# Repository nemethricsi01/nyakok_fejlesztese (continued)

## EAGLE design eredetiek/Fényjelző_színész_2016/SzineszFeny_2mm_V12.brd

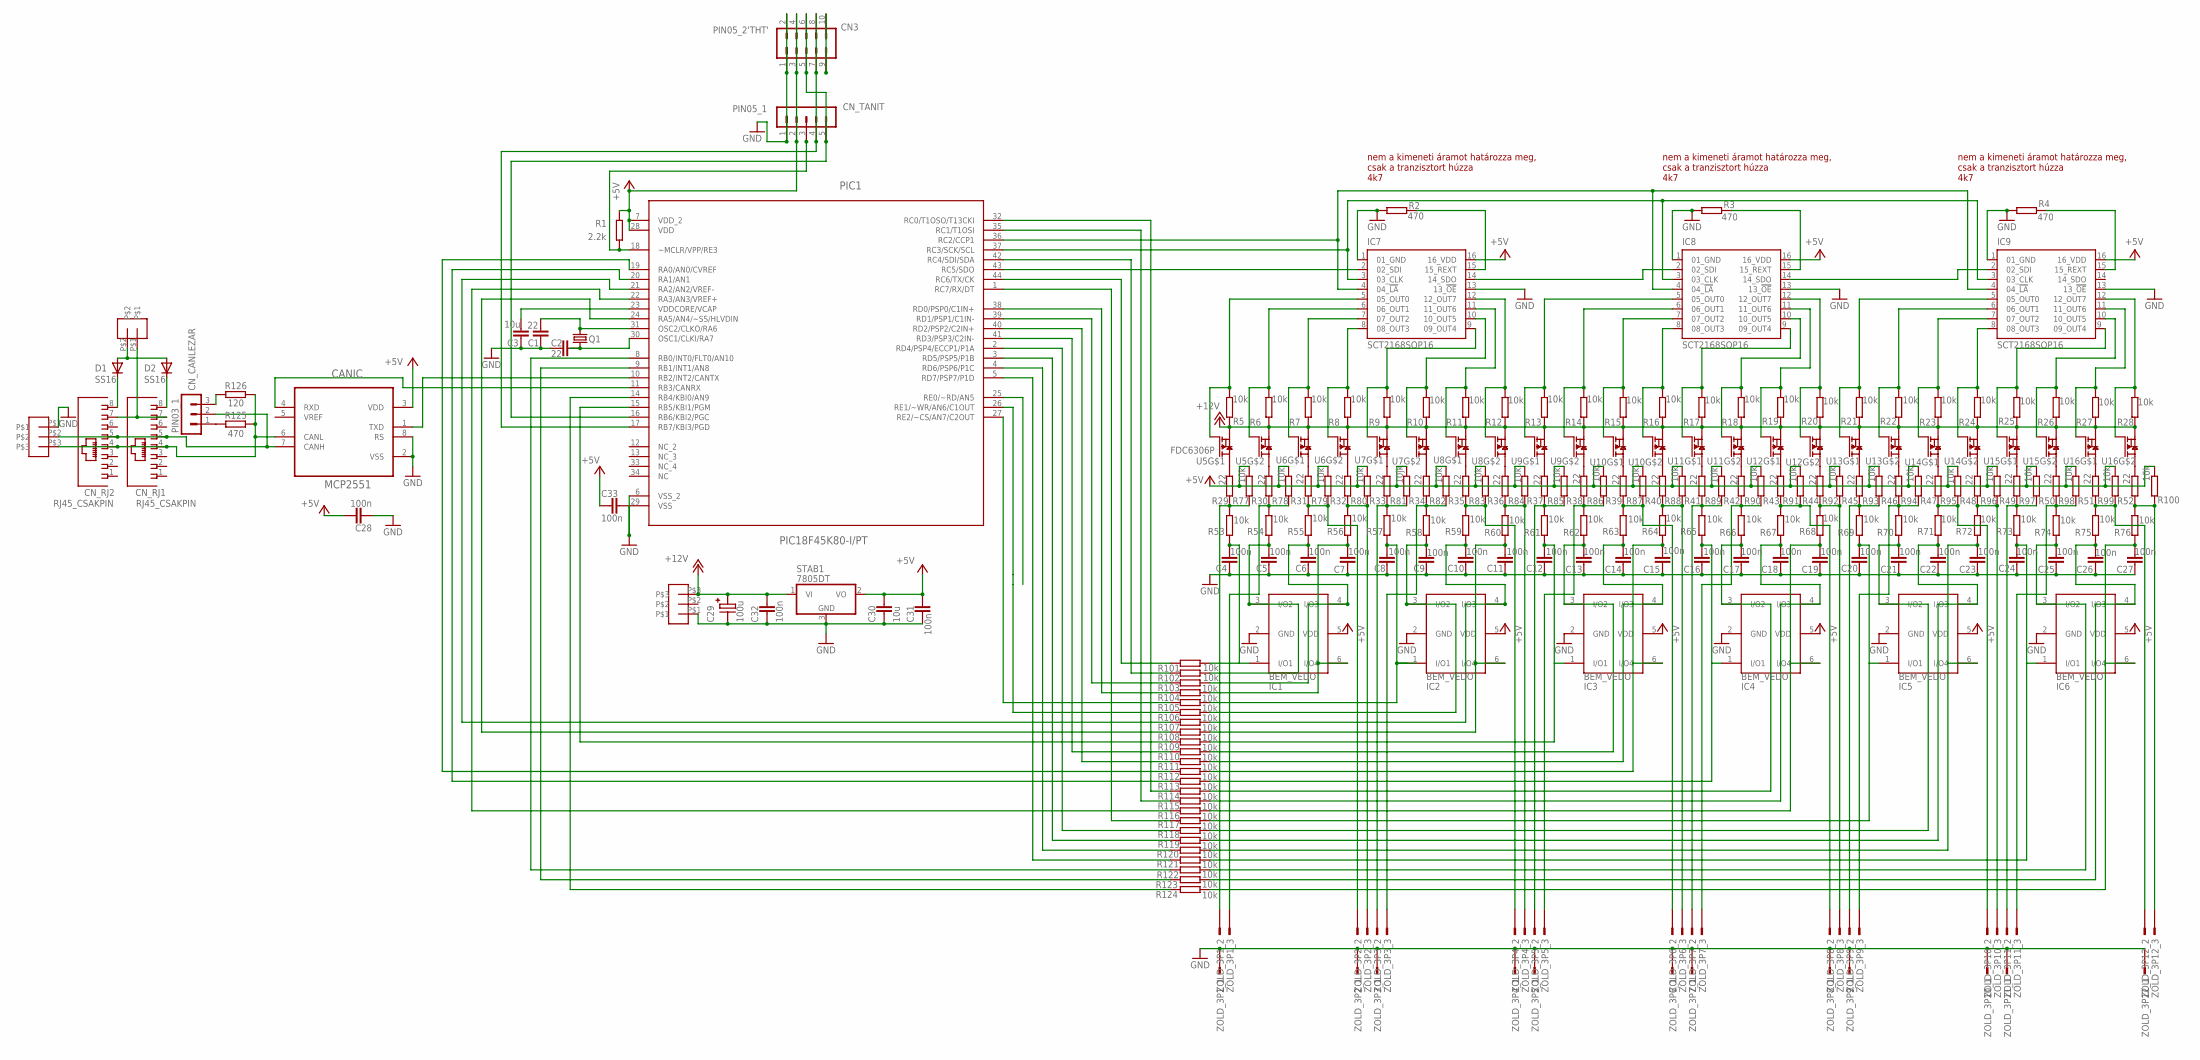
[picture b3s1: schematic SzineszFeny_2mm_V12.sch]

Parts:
C1, C2: 22; R0805
C3, C30: 10u; R0805
C4, C5, C6, C7, C8, C9, C10, C11, C12, C13, C14, C15, C16, C17, C18, C19, C20, C21, C22, C23, C24, C25, C26, C27, C28, C31, C32, C33: 100n; R0805
C29: 100u; C_EL1RASZT07
CANIC: MCP2551; DIP254P762X432-8
CN3: PIN05_2'THT'; PIN05_2
CN_CANLEZAR: PIN03_1
CN_RJ1, CN_RJ2: RJ45_CSAKPIN
CN_TANIT: PIN05_1
D1, D2: SS16; DO214AC
IC1, IC2, IC3, IC4, IC5, IC6: BEM_VEDO; TSOP-6
IC7, IC8, IC9: SCT2168SOP16; SO16
PIC1: PIC18F45K80-I/PT; QFP80P1200X1200X120-44N
Q1: XTAL_2QS; XTAL_QS
R1: 2.2k; R0805@1
R2, R3, R4, R125: 470; R0805@1
R5, R6, R7, R8, R9, R10, R11, R12, R13, R14, R15, R16, R17, R18, R19, R20, R21, R22, R23, R24, R25, R26, R27, R28, R53, R54, R55, R56, R57, R58, R59, R60, R61, R62, R63, R64, R65, R66, R67, R68, R69, R70, R71, R72, R73, R74, R75, R76, R77, R78, R79, R80, R82, R83, R84, R85, R86, R87, R88, R89, R90, R91, R92, R93, R94, R95, R96, R97, R98, R99, R100, R101, R102, R103, R104, R105, R106, R107, R108, R109, R110, R111, R112, R113, R114, R115, R116, R117, R118, R119, R120, R121, R122, R123, R124: 10k; R0805@1
R29, R30, R31, R32, R33, R34, R35, R36, R37, R38, R39, R40, R41, R42, R43, R44, R45, R46, R47, R48, R49, R50, R51, R52: 22; R0805@1
R81: 10jk; R0805@1
R126: 120; R0805@1
STAB1: 7805DT; TO252
U5, U16: FDC6306P; SOT26
U6, U7, U8, U9, U10, U11, U12, U13, U14, U15: AP2625GY-HF-3SOT26; SOT26
U$1, U$20: FEHER_TUS_3
U$21: FEHER_TUS_2ALLO; FEHER_TUS_2
ZOLD_3P1, ZOLD_3P2, ZOLD_3P3, ZOLD_3P4, ZOLD_3P5, ZOLD_3P6, ZOLD_3P7, ZOLD_3P8, ZOLD_3P9, ZOLD_3P10, ZOLD_3P11, ZOLD_3P12: ZOLD_KICSI_3P

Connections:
+5V: C28.1, C30.1, C31.1, C33.2, CANIC.3 (VDD), CN3.3, CN3.4, CN_TANIT.2, IC1.5 (VDD), IC2.5 (VDD), IC3.5 (VDD), IC4.5 (VDD), IC5.5 (VDD), IC6.5 (VDD), IC7.16 (16_VDD), IC8.16 (16_VDD), IC9.16 (16_VDD), PIC1.7 (VDD_2), PIC1.28 (VDD), R1.2 (E), R77.1 (A), R78.1 (A), R79.1 (A), R80.1 (A), R81.1 (A), R82.1 (A), R83.1 (A), R84.1 (A), R85.1 (A), R86.1 (A), R87.1 (A), R88.1 (A), R89.1 (A), R90.1 (A), R91.1 (A), R92.1 (A), R93.1 (A), R94.1 (A), R95.1 (A), R96.1 (A), R97.1 (A), R98.1 (A), R99.1 (A), R100.1 (A), STAB1.2 (VO)
+12V: C29.P+, C32.1, R5.1 (A), R6.1 (A), R7.1 (A), R8.1 (A), R9.1 (A), R10.1 (A), R11.1 (A), R12.1 (A), R13.1 (A), R14.1 (A), R15.1 (A), R16.1 (A), R17.1 (A), R18.1 (A), R19.1 (A), R20.1 (A), R21.1 (A), R22.1 (A), R23.1 (A), R24.1 (A), R25.1 (A), R26.1 (A), R27.1 (A), R28.1 (A), STAB1.1 (VI), U5.P$2 (S), U5.P$5 (S), U6.P$2 (S), U6.P$5 (S), U7.P$2 (S), U7.P$5 (S), U8.P$2 (S), U8.P$5 (S), U9.P$2 (S), U9.P$5 (S), U10.P$2 (S), U10.P$5 (S), U11.P$2 (S), U11.P$5 (S), U12.P$2 (S), U12.P$5 (S), U13.P$2 (S), U13.P$5 (S), U14.P$2 (S), U14.P$5 (S), U15.P$2 (S), U15.P$5 (S), U16.P$2 (S), U16.P$5 (S), U$20.P$3
GND: C1.2, C2.2, C3.2, C4.2, C5.2, C6.2, C7.2, C8.2, C9.2, C10.2, C11.2, C12.2, C13.2, C14.2, C15.2, C16.2, C17.2, C18.2, C19.2, C20.2, C21.2, C22.2, C23.2, C24.2, C25.2, C26.2, C27.2, C28.2, C29.P-, C30.2, C31.2, C32.2, C33.1, CANIC.2 (VSS), CANIC.8 (RS), CN3.1, CN3.2, CN_TANIT.1, IC1.2 (GND), IC2.2 (GND), IC3.2 (GND), IC4.2 (GND), IC5.2 (GND), IC6.2 (GND), IC7.1 (01_GND), IC7.13 (13_!OE!), IC8.1 (01_GND), IC8.13 (13_!OE!), IC9.1 (01_GND), IC9.13 (13_!OE!), PIC1.6 (VSS_2), PIC1.29 (VSS), R2.1 (A), R3.1 (A), R4.1 (A), STAB1.3 (GND), U$1.P$1, U$20.P$1, ZOLD_3P1.1, ZOLD_3P2.1, ZOLD_3P3.1, ZOLD_3P4.1, ZOLD_3P5.1, ZOLD_3P6.1, ZOLD_3P7.1, ZOLD_3P8.1, ZOLD_3P9.1, ZOLD_3P10.1, ZOLD_3P11.1, ZOLD_3P12.1
unnamed: C3.1, PIC1.23 (VDDCORE/VCAP)
unnamed: CN_TANIT.3, PIC1.18 (~MCLR/VPP/RE3), R1.1 (A)
unnamed: CN3.7, CN3.8, CN_TANIT.4, PIC1.17 (RB7/KBI3/PGD)
unnamed: IC7.14 (14_SDO), IC8.2 (02_SDI)
unnamed: C1.1, PIC1.31 (OSC2/CLKO/RA6), Q1.2
unnamed: C2.1, PIC1.30 (OSC1/CLKI/RA7), Q1.1
unnamed: PIC1.19 (RA0/AN0/CVREF), R112.1 (A)
unnamed: PIC1.20 (RA1/AN1), R113.1 (A)
unnamed: PIC1.22 (RA3/AN3/VREF+), R116.1 (A)
unnamed: PIC1.21 (RA2/AN2/VREF-), R107.1 (A)
unnamed: PIC1.24 (RA5/AN4/~SS/HLVDIN), R108.1 (A)
unnamed: IC8.7 (07_OUT2), R15.2 (E), U10.P$1 (G)
unnamed: IC7.6 (06_OUT1), R6.2 (E), U5.P$3 (G)
unnamed: IC9.5 (05_OUT0), R21.2 (E), U13.P$1 (G)
unnamed: IC8.15 (15_REXT), R3.2 (E)
unnamed: IC8.5 (05_OUT0), R13.2 (E), U9.P$1 (G)
unnamed: IC7.3 (03_CLK), IC8.3 (03_CLK), IC9.3 (03_CLK), PIC1.37 (RC3/SCK/SCL)
unnamed: IC7.4 (04_!LA!), IC8.4 (04_!LA!), IC9.4 (04_!LA!), PIC1.36 (RC2/CCP1)
unnamed: IC9.6 (06_OUT1), R22.2 (E), U13.P$3 (G)
unnamed: IC9.7 (07_OUT2), R23.2 (E), U14.P$1 (G)
unnamed: IC7.8 (08_OUT3), R8.2 (E), U6.P$3 (G)
unnamed: IC9.15 (15_REXT), R4.2 (E)
unnamed: CN_CANLEZAR.1, R125.2 (E)
unnamed: IC9.8 (08_OUT3), R24.2 (E), U14.P$3 (G)
unnamed: IC8.6 (06_OUT1), R14.2 (E), U9.P$3 (G)
unnamed: IC7.5 (05_OUT0), R5.2 (E), U5.P$1 (G)
unnamed: IC7.7 (07_OUT2), R7.2 (E), U6.P$1 (G)
unnamed: IC8.8 (08_OUT3), R16.2 (E), U10.P$3 (G)
unnamed: IC9.9 (09_OUT4), R25.2 (E), U15.P$1 (G)
unnamed: IC8.9 (09_OUT4), R17.2 (E), U11.P$1 (G)
unnamed: IC9.10 (10_OUT5), R26.2 (E), U15.P$3 (G)
unnamed: IC8.10 (10_OUT5), R18.2 (E), U11.P$3 (G)
unnamed: IC7.9 (09_OUT4), R9.2 (E), U7.P$1 (G)
unnamed: IC9.11 (11_OUT6), R27.2 (E), U16.P$1 (G)
unnamed: IC8.11 (11_OUT6), R19.2 (E), U12.P$1 (G)
unnamed: IC8.12 (12_OUT7), R20.2 (E), U12.P$3 (G)
unnamed: IC7.10 (10_OUT5), R10.2 (E), U7.P$3 (G)
unnamed: IC7.11 (11_OUT6), R11.2 (E), U8.P$1 (G)
unnamed: IC7.12 (12_OUT7), R12.2 (E), U8.P$3 (G)
unnamed: IC9.12 (12_OUT7), R28.2 (E), U16.P$3 (G)
unnamed: R29.2 (E), U5.P$6 (D)
unnamed: R30.2 (E), U5.P$4 (D)
unnamed: R31.2 (E), U6.P$6 (D)
unnamed: R32.2 (E), U6.P$4 (D)
unnamed: R33.2 (E), U7.P$6 (D)
unnamed: R34.2 (E), U7.P$4 (D)
unnamed: R35.2 (E), U8.P$6 (D)
unnamed: R36.2 (E), U8.P$4 (D)
unnamed: R37.2 (E), U9.P$6 (D)
unnamed: R38.2 (E), U9.P$4 (D)
unnamed: R39.2 (E), U10.P$6 (D)
unnamed: R40.2 (E), U10.P$4 (D)
unnamed: R41.2 (E), U11.P$6 (D)
unnamed: R42.2 (E), U11.P$4 (D)
unnamed: R43.2 (E), U12.P$6 (D)
unnamed: R44.2 (E), U12.P$4 (D)
unnamed: R45.2 (E), U13.P$6 (D)
unnamed: R46.2 (E), U13.P$4 (D)
unnamed: R47.2 (E), U14.P$6 (D)
unnamed: R48.2 (E), U14.P$4 (D)
unnamed: R49.2 (E), U15.P$6 (D)
unnamed: R50.2 (E), U15.P$4 (D)
unnamed: IC7.2 (02_SDI), PIC1.43 (RC5/SDO)
unnamed: R51.2 (E), U16.P$6 (D)
unnamed: R52.2 (E), U16.P$4 (D)
unnamed: CN3.5, CN3.6, CN_TANIT.5, PIC1.16 (RB6/KBI2/PGC)
unnamed: PIC1.27 (RE2/~CS/AN7/C2OUT), R105.1 (A)
unnamed: R31.1 (A), R55.2 (E), R79.2 (E), ZOLD_3P2.2
unnamed: R32.1 (A), R56.2 (E), R80.2 (E), ZOLD_3P2.3
unnamed: R33.1 (A), R57.2 (E), R81.2 (E), ZOLD_3P3.2
unnamed: PIC1.26 (RE1/~WR/AN6/C1OUT), R106.1 (A)
unnamed: R35.1 (A), R59.2 (E), R83.2 (E), ZOLD_3P4.2
unnamed: R36.1 (A), R60.2 (E), R84.2 (E), ZOLD_3P4.3
unnamed: R37.1 (A), R61.2 (E), R85.2 (E), ZOLD_3P5.2
unnamed: R38.1 (A), R62.2 (E), R86.2 (E), ZOLD_3P5.3
unnamed: R39.1 (A), R63.2 (E), R87.2 (E), ZOLD_3P6.2
unnamed: R40.1 (A), R64.2 (E), R88.2 (E), ZOLD_3P6.3
unnamed: R41.1 (A), R65.2 (E), R89.2 (E), ZOLD_3P7.2
unnamed: R42.1 (A), R66.2 (E), R90.2 (E), ZOLD_3P7.3
unnamed: R43.1 (A), R67.2 (E), R91.2 (E), ZOLD_3P8.2
unnamed: R44.1 (A), R68.2 (E), R92.2 (E), ZOLD_3P8.3
unnamed: R45.1 (A), R69.2 (E), R93.2 (E), ZOLD_3P9.2
unnamed: R46.1 (A), R70.2 (E), R94.2 (E), ZOLD_3P9.3
unnamed: R47.1 (A), R71.2 (E), R95.2 (E), ZOLD_3P10.2
unnamed: R48.1 (A), R72.2 (E), R96.2 (E), ZOLD_3P10.3
unnamed: R49.1 (A), R73.2 (E), R97.2 (E), ZOLD_3P11.2
unnamed: IC7.15 (15_REXT), R2.2 (E)
unnamed: R50.1 (A), R74.2 (E), R98.2 (E), ZOLD_3P11.3
unnamed: R51.1 (A), R75.2 (E), R99.2 (E), ZOLD_3P12.2
unnamed: R52.1 (A), R76.2 (E), R100.2 (E), ZOLD_3P12.3
unnamed: C4.1, IC1.1 (I/O1), R53.1 (A), R101.2 (E)
unnamed: R29.1 (A), R53.2 (E), R77.2 (E), ZOLD_3P1.2
unnamed: C5.1, IC1.3 (I/O2), R54.1 (A), R102.2 (E)
unnamed: C6.1, IC1.4 (I/O3), R55.1 (A), R103.2 (E)
unnamed: C7.1, IC1.6 (I/O4), R56.1 (A), R104.2 (E)
unnamed: C11.1, IC2.6 (I/O4), R60.1 (A), R108.2 (E)
unnamed: R34.1 (A), R58.2 (E), R82.2 (E), ZOLD_3P3.3
unnamed: C8.1, IC2.1 (I/O1), R57.1 (A), R105.2 (E)
unnamed: CANIC.6 (CANL), CN_RJ1.4, CN_RJ2.4, R125.1 (A), R126.2 (E), U$1.P$3
unnamed: C12.1, IC3.1 (I/O1), R61.1 (A), R109.2 (E)
unnamed: C13.1, IC3.3 (I/O2), R62.1 (A), R110.2 (E)
unnamed: C17.1, IC4.3 (I/O2), R66.1 (A), R114.2 (E)
unnamed: C15.1, IC3.6 (I/O4), R64.1 (A), R112.2 (E)
unnamed: C16.1, IC4.1 (I/O1), R65.1 (A), R113.2 (E)
unnamed: R30.1 (A), R54.2 (E), R78.2 (E), ZOLD_3P1.3
unnamed: C18.1, IC4.4 (I/O3), R67.1 (A), R115.2 (E)
unnamed: C19.1, IC4.6 (I/O4), R68.1 (A), R116.2 (E)
unnamed: C20.1, IC5.1 (I/O1), R69.1 (A), R117.2 (E)
unnamed: C21.1, IC5.3 (I/O2), R70.1 (A), R118.2 (E)
unnamed: C22.1, IC5.4 (I/O3), R71.1 (A), R119.2 (E)
unnamed: C23.1, IC5.6 (I/O4), R72.1 (A), R120.2 (E)
unnamed: C24.1, IC6.1 (I/O1), R73.1 (A), R121.2 (E)
unnamed: C25.1, IC6.3 (I/O2), R74.1 (A), R122.2 (E)
unnamed: C26.1, IC6.4 (I/O3), R75.1 (A), R123.2 (E)
unnamed: C27.1, IC6.6 (I/O4), R76.1 (A), R124.2 (E)
unnamed: PIC1.5 (RD7/PSP7/P1D), R121.1 (A)
unnamed: PIC1.4 (RD6/PSP6/P1C), R120.1 (A)
unnamed: C14.1, IC3.4 (I/O3), R63.1 (A), R111.2 (E)
unnamed: PIC1.3 (RD5/PSP5/P1B), R119.1 (A)
unnamed: PIC1.2 (RD4/PSP4/ECCP1/P1A), R118.1 (A)
unnamed: PIC1.41 (RD3/PSP3/C2IN-), R110.1 (A)
unnamed: PIC1.40 (RD2/PSP2/C2IN+), R111.1 (A)
unnamed: PIC1.39 (RD1/PSP1/C1IN-), R103.1 (A)
unnamed: PIC1.38 (RD0/PSP0/C1IN+), R104.1 (A)
unnamed: PIC1.1 (RC7/RX/DT), R117.1 (A)
unnamed: PIC1.44 (RC6/TX/CK), R101.1 (A)
unnamed: PIC1.42 (RC4/SDI/SDA), R102.1 (A)
unnamed: PIC1.35 (RC1/T1OSI), R115.1 (A)
unnamed: PIC1.32 (RC0/T1OSO/T13CKI), R114.1 (A)
unnamed: CANIC.7 (CANH), CN_CANLEZAR.2, CN_RJ1.5, CN_RJ2.5, U$1.P$2
unnamed: CANIC.1 (TXD), PIC1.10 (RB2/INT2/CANTX)
unnamed: C10.1, IC2.4 (I/O3), R59.1 (A), R107.2 (E)
unnamed: C9.1, IC2.3 (I/O2), R58.1 (A), R106.2 (E)
unnamed: PIC1.15 (RB5/KBI1/PGM), R109.1 (A)
unnamed: PIC1.14 (RB4/KBI0/AN9), R124.1 (A)
unnamed: CANIC.4 (RXD), PIC1.11 (RB3/CANRX)
unnamed: CN_CANLEZAR.3, R126.1 (A)
unnamed: PIC1.9 (RB1/INT1/AN8), R123.1 (A)
unnamed: PIC1.8 (RB0/INT0/FLT0/AN10), R122.1 (A)
unnamed: CN3.9, CN3.10
unnamed: IC8.14 (14_SDO), IC9.2 (02_SDI)
unnamed: CN_RJ2.8, D1.C
unnamed: CN_RJ1.7, CN_RJ2.7, U$21.P$1
unnamed: D1.A, D2.A, U$21.P$2
unnamed: CN_RJ1.8, D2.C

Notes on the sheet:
nem a kimeneti áramot határozza meg, csak a tranzisztort húzza 4k7

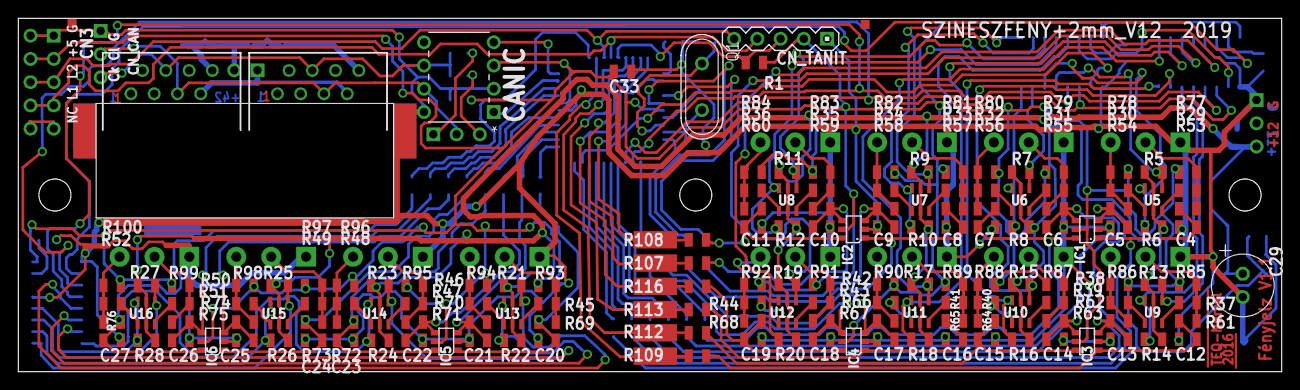
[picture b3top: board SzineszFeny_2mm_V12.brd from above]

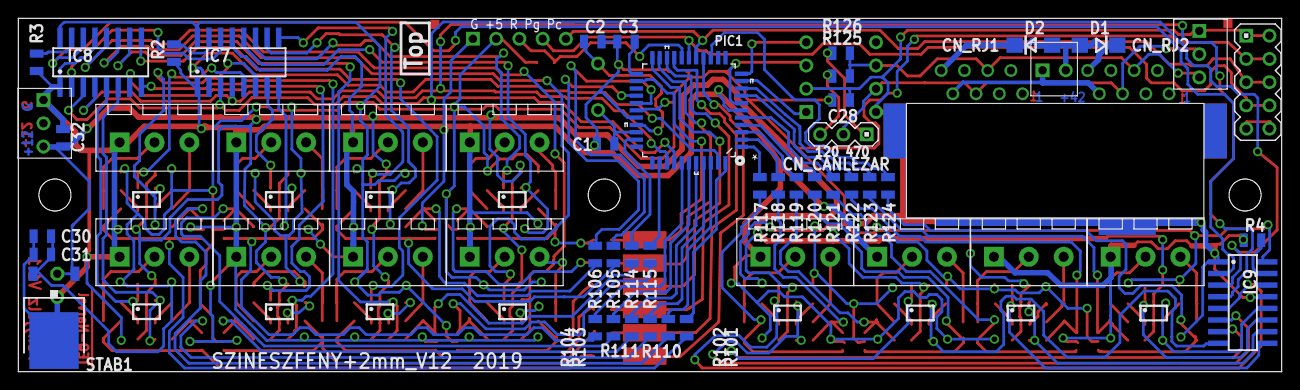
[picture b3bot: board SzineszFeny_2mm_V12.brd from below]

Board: 2 copper layers, 138.0 x 38.6 mm, 206 parts (54 on the bottom side), 148 nets.

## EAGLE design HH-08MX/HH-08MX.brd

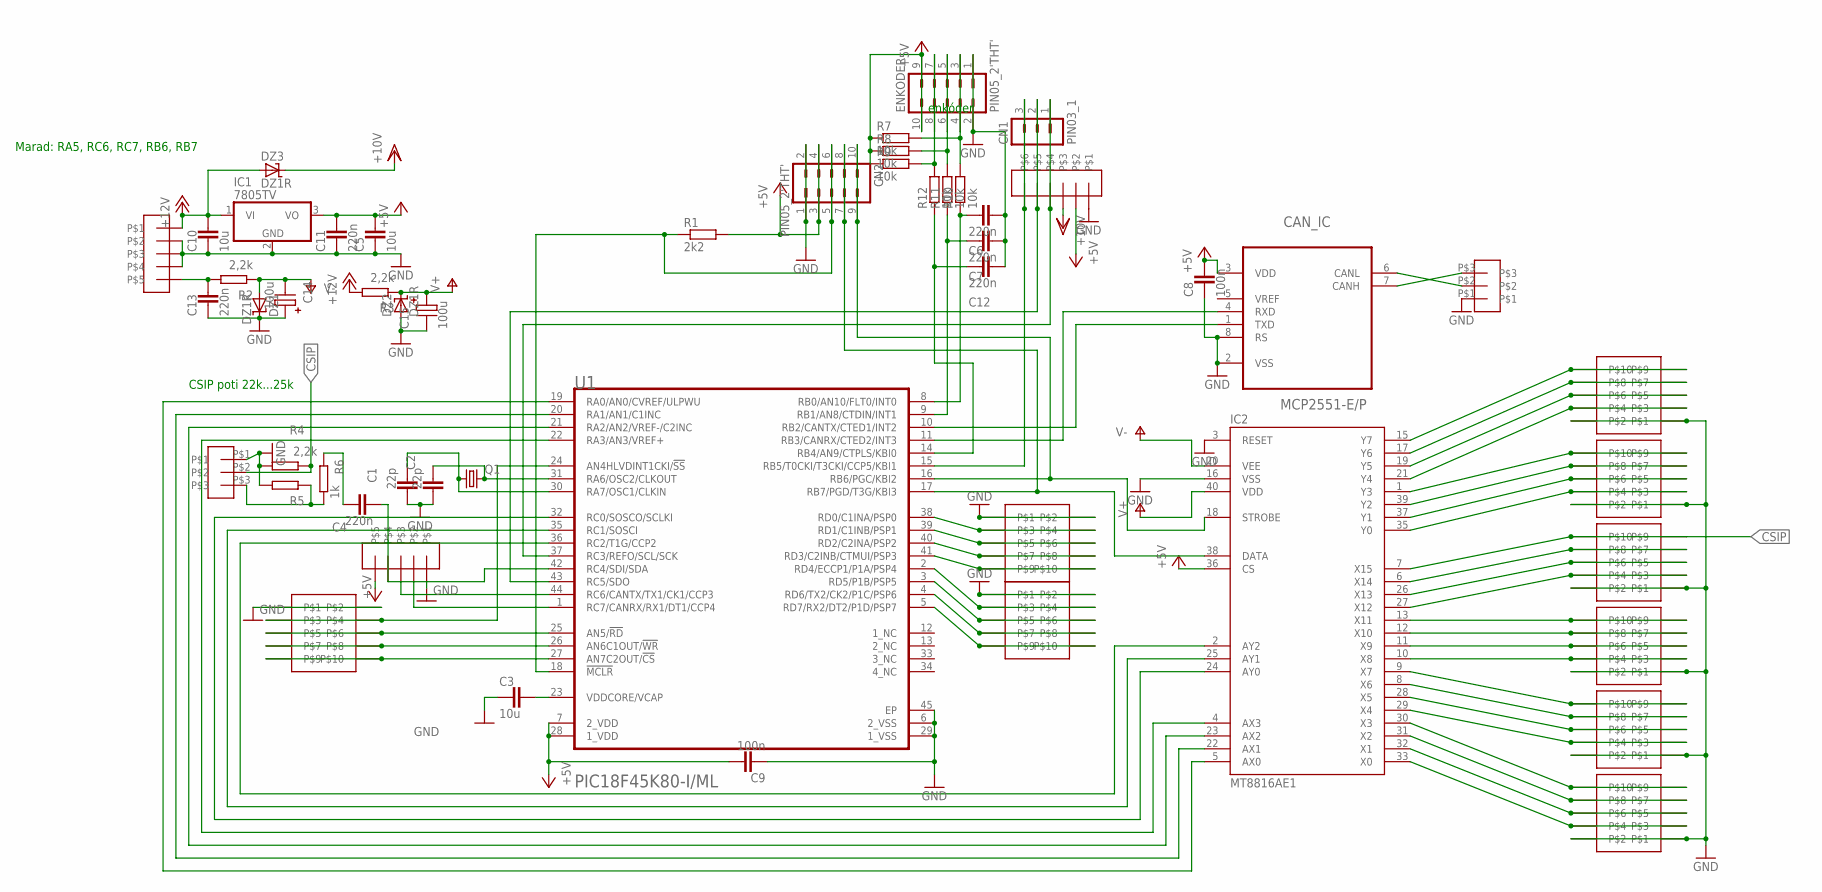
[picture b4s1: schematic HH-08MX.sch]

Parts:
BE1-4, BE5-8, BE9-12, BE13-16: KERETES_TUS_10
C1, C2: 22p; R_0805_NAGY
C3, C5, C10: 10u; R_0805_NAGY
C4, C6, C7, C11, C12, C13: 220n; R_0805_NAGY
C8, C9: 100n; R_0805_NAGY
C14, C15: 100u; C_EL1RASZT06
CAN_IC: MCP2551-E/P; DIP254P762X432-8
CN1: PIN03_1
CN2: PIN05_2'THT'; PIN05_2
DZ1, DZ2, DZ3: DZ1R; D1RASZT
ENKODER: PIN05_2'THT'; PIN05_2
IC1: 7805TV; TO220V
IC2: MT8816AE1; DIL40
KI1-4, KI5-8: KERETES_TUS_10
KIJELZO: FEHER_TUS_6
Q1: XTAL_2QS; XTAL_QS
R1: 2k2; R0805
R2, R3, R4: 2,2k; R_0805_NAGY
R5: R_EU0805_NAGY; R_0805_NAGY
R6: 1k; R_0805_NAGY
R7, R8, R9, R10, R11, R12: 10k; R0805
SOROSPORT: FEHER_TUS_5
U1: MICROCHIP_PIC18F45K80-I-MLMICROCHIP_PIC18F45K80-I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; MICROCHIP_PIC18F45K80-I-ML_2
U$1, U$4: FEHER_TUS_3
U$5: FEHER_TUS_5
U$14, U$15, U$16: KERETES_TUS_10

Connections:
+5V: C5.1, C8.1, C9.1, C11.1, CAN_IC.3 (VDD), CN2.3, CN2.4, ENKODER.9, ENKODER.10, IC1.3 (VO), IC2.36 (CS), KIJELZO.P$2, R1.2, R7.1, R8.1, R9.1, SOROSPORT.P$5, U1.7 (2_VDD), U1.28 (1_VDD)
+12V: C10.1, DZ3.P$1 (A), IC1.1 (VI), R3.2 (E), U$5.P$1
CSIP: BE13-16.P$9, BE13-16.P$10, IC2.7 (X15), R4.1 (A), U$1.P$2
GND: BE1-4.P$1, BE1-4.P$2, BE5-8.P$1, BE5-8.P$2, BE9-12.P$1, BE9-12.P$2, BE13-16.P$1, BE13-16.P$2, C1.1, C2.1, C3.2, C5.2, C6.1, C7.1, C8.2, C9.2, C10.2, C11.2, C12.1, C13.2, C14.P+, C15.P-, CAN_IC.2 (VSS), CAN_IC.8 (RS), CN2.1, CN2.2, DZ1.P$2 (C), DZ2.P$1 (A), ENKODER.1, ENKODER.2, IC1.2 (GND), IC2.3 (RESET), IC2.16 (VSS), KI1-4.P$1, KI1-4.P$2, KI5-8.P$1, KI5-8.P$2, KIJELZO.P$1, R4.2 (E), R5.2 (E), SOROSPORT.P$1, U1.6 (2_VSS), U1.29 (1_VSS), U1.45 (EP), U$1.P$1, U$4.P$1, U$5.P$2, U$5.P$3, U$5.P$4, U$14.P$1, U$14.P$2, U$15.P$1, U$15.P$2, U$16.P$1, U$16.P$2
unnamed: CN2.5, CN2.6, R1.1, U1.18 (!MCLR!)
unnamed: CN1.1, KIJELZO.P$4, U1.37 (RC3/REFO/SCL/SCK)
unnamed: CN2.9, CN2.10, IC2.18 (STROBE), U1.16 (RB6/PGC/KBI2)
unnamed: C12.2, R12.1, U1.14 (RB4/AN9/CTPLS/KBI0)
unnamed: CAN_IC.1 (TXD), U1.10 (RB2/CANTX/CTED1/INT2)
unnamed: C7.2, R11.1, U1.9 (RB1/AN8/CTDIN/INT1)
unnamed: CAN_IC.7 (CANH), U$4.P$3
unnamed: CAN_IC.6 (CANL), U$4.P$2
unnamed: IC2.15 (Y7), KI5-8.P$9, KI5-8.P$10
unnamed: C2.2, Q1.2, U1.31 (RA6/OSC2/CLKOUT)
unnamed: C1.2, Q1.1, U1.30 (RA7/OSC1/CLKIN)
unnamed: IC2.17 (Y6), KI5-8.P$7, KI5-8.P$8
unnamed: IC2.19 (Y5), KI5-8.P$5, KI5-8.P$6
unnamed: CAN_IC.4 (RXD), U1.11 (RB3/CANRX/CTED2/INT3)
unnamed: C3.1, U1.23 (VDDCORE/VCAP)
unnamed: C6.2, R10.1, U1.8 (RB0/AN10/FLT0/INT0)
unnamed: IC2.21 (Y4), KI5-8.P$3, KI5-8.P$4
unnamed: CN1.2, KIJELZO.P$5, U1.43 (RC5/SDO)
unnamed: CN1.3, KIJELZO.P$6, U1.15 (RB5/T0CKI/T3CKI/CCP5/KBI1)
unnamed: U1.38 (RD0/C1INA/PSP0), U$14.P$3, U$14.P$4
unnamed: CN2.7, CN2.8, IC2.38 (DATA), U1.17 (RB7/PGD/T3G/KBI3)
unnamed: U1.39 (RD1/C1INB/PSP1), U$14.P$5, U$14.P$6
unnamed: C13.1, R2.2 (E), U$5.P$5
unnamed: U1.40 (RD2/C2INA/PSP2), U$14.P$7, U$14.P$8
unnamed: U1.41 (RD3/C2INB/CTMUI/PSP3), U$14.P$9, U$14.P$10
unnamed: U1.2 (RD4/ECCP1/P1A/PSP4), U$15.P$3, U$15.P$4
unnamed: U1.3 (RD5/P1B/PSP5), U$15.P$5, U$15.P$6
unnamed: U1.4 (RD6/TX2/CK2/P1C/PSP6), U$15.P$7, U$15.P$8
unnamed: U1.5 (RD7/RX2/DT2/P1D/PSP7), U$15.P$9, U$15.P$10
unnamed: IC2.1 (Y3), KI1-4.P$9, KI1-4.P$10
unnamed: IC2.39 (Y2), KI1-4.P$7, KI1-4.P$8
unnamed: U1.27 (AN7C2OUT/!CS!), U$16.P$9, U$16.P$10
unnamed: U1.26 (AN6C1OUT/!WR!), U$16.P$7, U$16.P$8
unnamed: U1.25 (AN5/!RD!), U$16.P$5, U$16.P$6
unnamed: U1.24 (AN4HLVDINT1CKI/!SS!), U$16.P$3, U$16.P$4
unnamed: SOROSPORT.P$2, U1.1 (RC7/CANRX/RX1/DT1/CCP4)
unnamed: SOROSPORT.P$3, U1.44 (RC6/CANTX/TX1/CK1/CCP3)
unnamed: IC2.37 (Y1), KI1-4.P$5, KI1-4.P$6
unnamed: C4.1, SOROSPORT.P$4, U1.42 (RC4/SDI/SDA)
unnamed: IC2.35 (Y0), KI1-4.P$3, KI1-4.P$4
unnamed: ENKODER.5, ENKODER.6, R8.2, R11.2
unnamed: BE13-16.P$7, BE13-16.P$8, IC2.6 (X14)
unnamed: BE13-16.P$5, BE13-16.P$6, IC2.26 (X13)
unnamed: BE13-16.P$3, BE13-16.P$4, IC2.27 (X12)
unnamed: BE9-12.P$9, BE9-12.P$10, IC2.13 (X11)
unnamed: BE9-12.P$7, BE9-12.P$8, IC2.12 (X10)
unnamed: BE9-12.P$5, BE9-12.P$6, IC2.11 (X9)
unnamed: BE9-12.P$3, BE9-12.P$4, IC2.10 (X8)
unnamed: BE5-8.P$9, BE5-8.P$10, IC2.9 (X7)
unnamed: BE5-8.P$7, BE5-8.P$8, IC2.8 (X6)
unnamed: BE5-8.P$5, BE5-8.P$6, IC2.28 (X5)
unnamed: BE5-8.P$3, BE5-8.P$4, IC2.29 (X4)
unnamed: BE1-4.P$9, BE1-4.P$10, IC2.30 (X3)
unnamed: BE1-4.P$7, BE1-4.P$8, IC2.31 (X2)
unnamed: BE1-4.P$5, BE1-4.P$6, IC2.32 (X1)
unnamed: BE1-4.P$3, BE1-4.P$4, IC2.33 (X0)
unnamed: ENKODER.7, ENKODER.8, R9.2, R12.2
unnamed: R5.1 (A), R6.2 (E), U$1.P$3
unnamed: C4.2, R6.1 (A)
unnamed: ENKODER.3, ENKODER.4, R7.2, R10.2
unnamed: IC2.24 (AY0), U1.32 (RC0/SOSCO/SCLKI)
unnamed: IC2.25 (AY1), U1.35 (RC1/SOSCI)
unnamed: IC2.2 (AY2), U1.36 (RC2/T1G/CCP2)
unnamed: IC2.4 (AX3), U1.22 (RA3/AN3/VREF+)
unnamed: IC2.23 (AX2), U1.21 (RA2/AN2/VREF-/C2INC)
unnamed: IC2.22 (AX1), U1.20 (RA1/AN1/C1INC)
unnamed: IC2.5 (AX0), U1.19 (RA0/AN0/CVREF/ULPWU)
V+: C15.P+, DZ2.P$2 (C), IC2.40 (VDD), R3.1 (A)
V-: C14.P-, DZ1.P$1 (A), IC2.20 (VEE), R2.1 (A)
VDD: DZ3.P$2 (C), KIJELZO.P$3

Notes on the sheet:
Marad: RA5, RC6, RC7, RB6, RB7
enkóder
CSIP poti 22k...25k

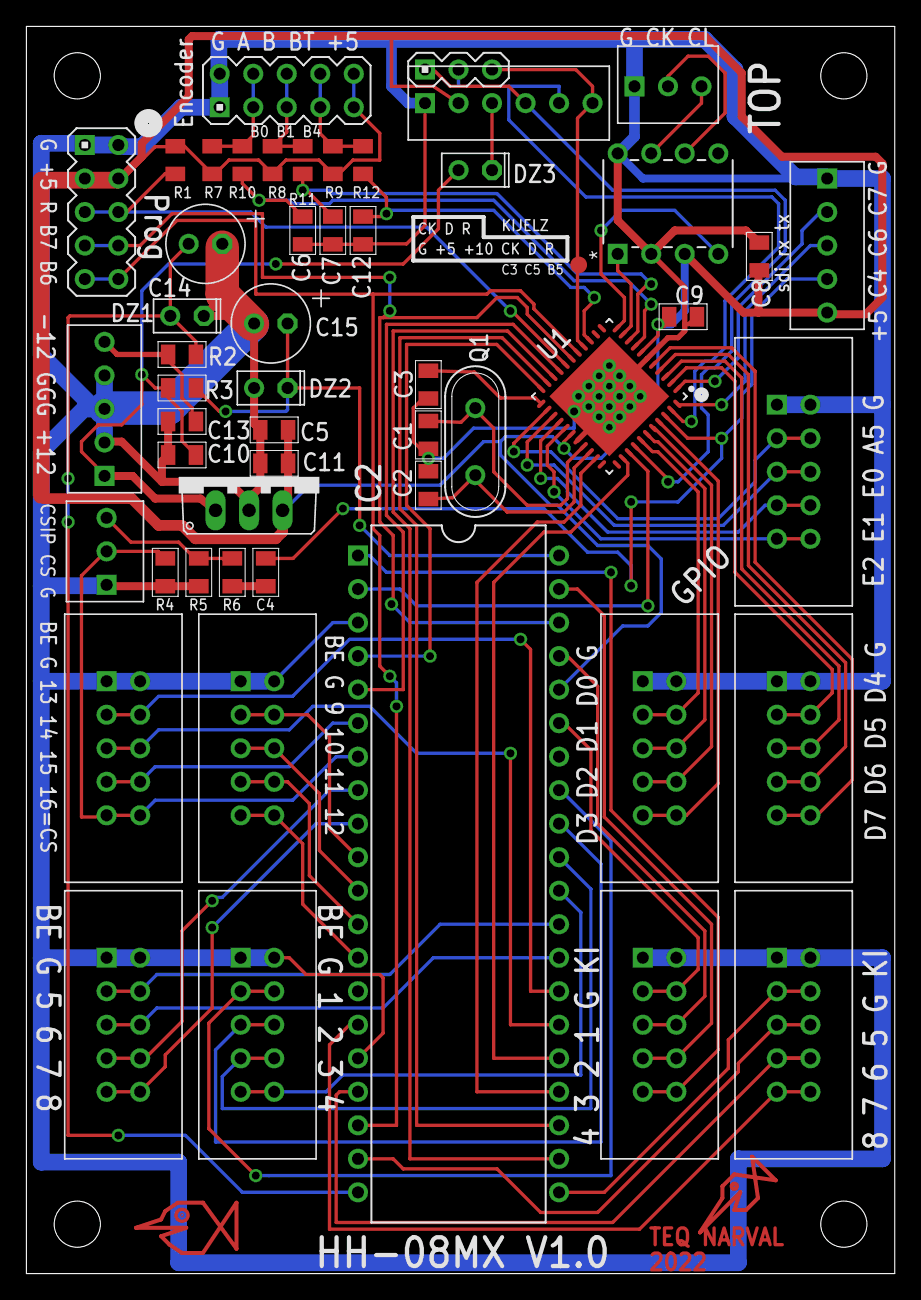
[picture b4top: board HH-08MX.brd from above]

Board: 2 copper layers, 65.8 x 94.5 mm, 52 parts (0 on the bottom side), 74 nets.

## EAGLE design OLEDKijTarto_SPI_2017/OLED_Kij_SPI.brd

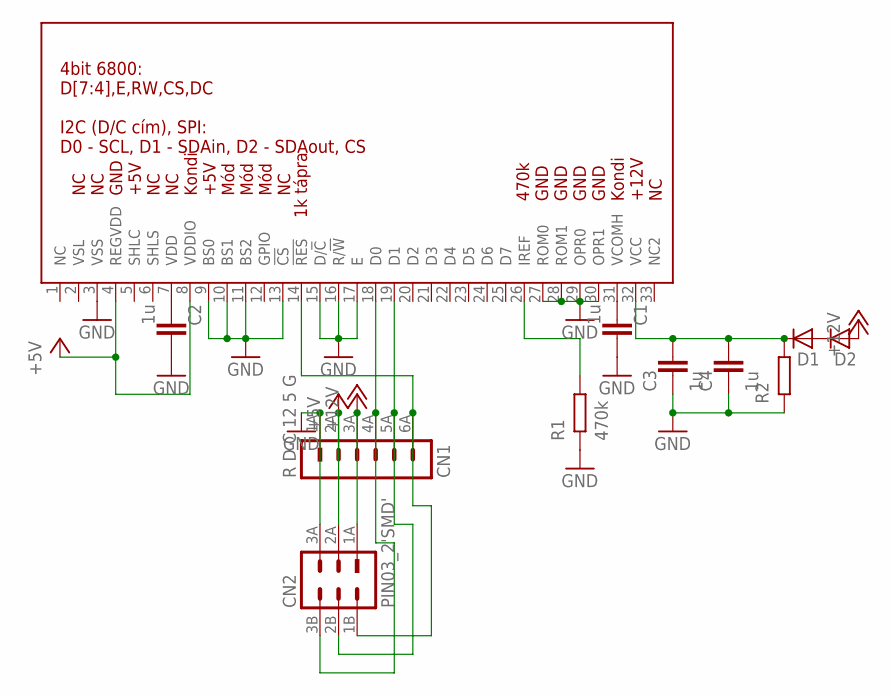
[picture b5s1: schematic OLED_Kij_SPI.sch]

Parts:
C1, C2, C3, C4: 1u; R0805
CN1: R D C 12 5 G; PIN_HEADER_1X6
CN2: PIN03_2'SMD'; PIN_HEADER_2X3
D1, D2: D0805
R1: 470k; R0805
R2: R_EU0805; R0805
U$1: OLED_DISPL

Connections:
+5V: CN1.2A (2), CN2.2A (3), U$1.4 (REGVDD), U$1.8 (VDDIO)
+12V: CN1.3A (3), CN2.1A (1), D2.1 (A)
GND: C1.1, C2.1, C3.2, C4.2, CN1.1A (1), CN2.3A (5), R1.1 (A), R2.1 (A), U$1.3 (VSS), U$1.9 (BS0), U$1.10 (BS1), U$1.11 (BS2), U$1.13 (!CS), U$1.15 (D/!C), U$1.16 (R/!W), U$1.17 (E), U$1.27 (ROM0), U$1.28 (ROM1), U$1.29 (OPR0), U$1.30 (OPR1)
unnamed: C1.2, U$1.31 (VCOMH)
unnamed: C2.2, U$1.7 (VDD)
unnamed: D1.1 (A), D2.2 (C)
unnamed: C3.1, C4.1, D1.2 (C), R2.2 (E), U$1.32 (VCC)
unnamed: R1.2 (E), U$1.26 (IREF)
unnamed: CN1.4A (4), CN2.3B (6), U$1.18 (D0)
unnamed: CN1.5A (5), CN2.2B (4), U$1.19 (D1)
unnamed: CN1.6A (6), CN2.1B (2), U$1.14 (!RES)

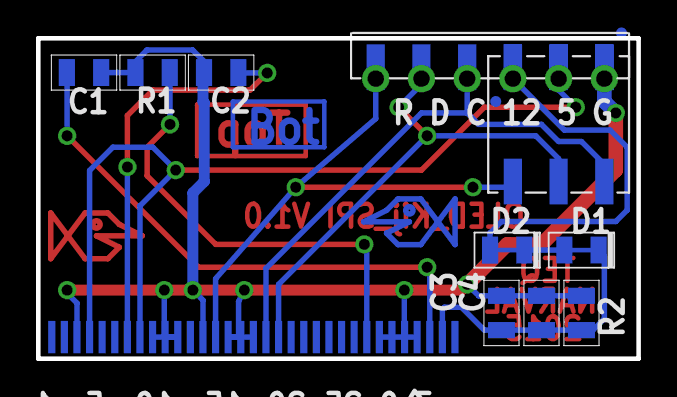
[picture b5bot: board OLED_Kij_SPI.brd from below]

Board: 2 copper layers, 33.4 x 17.8 mm, 11 parts (11 on the bottom side), 11 nets.

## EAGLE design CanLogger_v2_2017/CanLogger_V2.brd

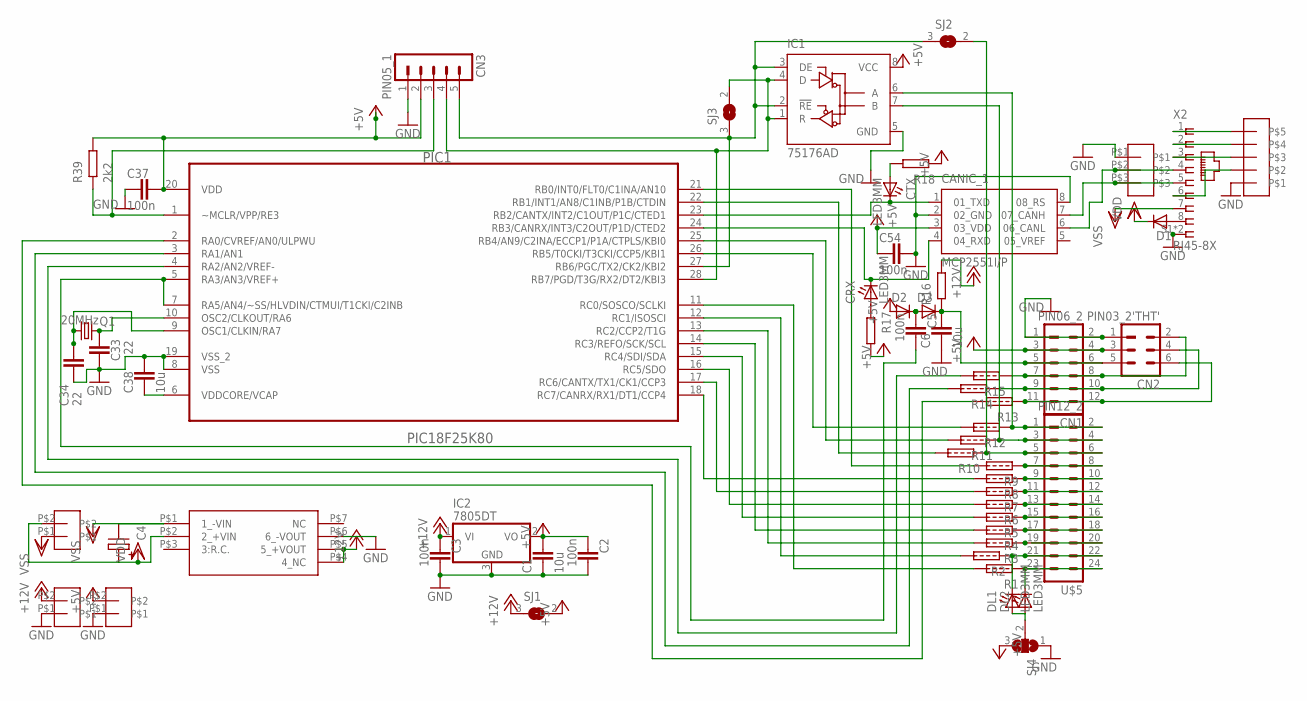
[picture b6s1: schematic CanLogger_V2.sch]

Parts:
C1, C6, C38: 10u; R0805
C2, C3, C5, C37, C54: 100n; R0805
C4: C_EL1R05; C_EL1RASZT05
C33, C34: 22; R0805
CANIC_1: MCP2551I/P; DIL_8
CN1: PIN06_2
CN2: PIN03_2'THT'; PIN03_2
CN3: PIN05_1
CN_CAN: FEHER_TUS_3
CRX: LED3MM
CTX: LED3MM
D1: D1R; D1RASZT
D2, D3: D0805
DL1, DL2: LED3MM
IC1: 75176AD; D_R-PDSO-G8
IC2: 7805DT; TO252
PIC1: PIC18F25K80; SOIC127P1030X265-28N
Q1: 20MHz; XTAL_QS
R1, R2, R3, R4, R5, R6, R7, R8, R9, R10, R11, R12, R13, R14, R15: RNULL_EU0805; R0805_C
R16, R17, R18: R_EU0805; R0805
R39: 2k2; R0805
SJ1, SJ2, SJ3: SJ
SJ4: SJ2W; SJ2
U$1: FEHER_TUS_5
U$2, U$3, U$4: FEHER_TUS_2ALLO; FEHER_TUS_2
U$5: PIN12_2
U$6: SPA02C
X2: RJ45-8X; RJ45

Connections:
+5V: C1.1, C2.2, C37.1, C54.2, CANIC_1.3 (03_VDD), CN1.3, CN1.4, CN2.3, CN3.2, D2.1 (A), IC1.8 (VCC), IC2.2 (VO), PIC1.20 (VDD), R17.2 (E), R18.1 (A), R39.2 (E), SJ1.2, SJ4.3, U$4.P$2
+12V: C3.2, IC2.1 (VI), R16.2 (E), SJ1.3 (1), U$3.P$2, U$6.P$4 (4_NC), U$6.P$5 (5_+VOUT)
GND: C1.2, C2.1, C3.1, C6.2, C33.2, C34.2, C37.2, C38.1, C54.1, CANIC_1.2 (02_GND), CANIC_1.8 (08_RS), CN1.1, CN1.2, CN2.1, CN3.1, CN_CAN.P$1, IC1.5 (GND), IC2.3 (GND), PIC1.8 (VSS), PIC1.19 (VSS_2), SJ4.1, U$1.P$1, U$3.P$1, U$4.P$1, U$6.P$6 (6_-VOUT), X2.S1 (S), X2.S2 (S)
unnamed: CANIC_1.7 (07_CANH), CN_CAN.P$3, X2.5
unnamed: IC1.7 (B), R11.1 (A), U$5.3, U$5.4
unnamed: CANIC_1.6 (06_CANL), CN_CAN.P$2, X2.4
unnamed: CN3.3, PIC1.1 (~MCLR/VPP/RE3), R39.1 (A)
unnamed: IC1.6 (A), R12.1 (A), U$5.1, U$5.2
unnamed: R10.1 (A), SJ2.2, U$5.5, U$5.6
unnamed: CANIC_1.1 (01_TXD), CTX.K (C), PIC1.23 (RB2/CANTX/INT2/C1OUT/P1C/CTED1)
unnamed: D1.P$1 (A), X2.8
unnamed: DL1.K (C), R2.1 (A), U$5.21, U$5.22
unnamed: R3.1 (A), U$5.19
unnamed: R4.1 (A), U$5.17, U$5.18
unnamed: R5.1 (A), U$5.15, U$5.16
unnamed: DL1.A, DL2.A, SJ4.2
unnamed: R6.1 (A), U$5.13, U$5.14
unnamed: R7.1 (A), U$5.11, U$5.12
unnamed: R8.1 (A), U$5.9, U$5.10
unnamed: R9.1 (A), U$5.7, U$5.8
unnamed: CRX.A, R17.1 (A)
unnamed: CTX.A, R18.2 (E)
unnamed: CN1.11, CN1.12, CN2.6, R13.1 (A)
unnamed: CN1.9, CN1.10, CN2.4, R14.1 (A)
unnamed: CN1.7, CN1.8, CN2.2, R15.1 (A)
unnamed: C5.2, D2.2 (C), D3.1 (A)
unnamed: C6.1, CN1.5, CN1.6, CN2.5, D3.2 (C), R16.1 (A)
unnamed: DL2.K (C), R1.1 (A), U$5.23, U$5.24
unnamed: PIC1.26 (RB5/T0CKI/T3CKI/CCP5/KBI1), R12.2 (E)
unnamed: PIC1.18 (RC7/CANRX/RX1/DT1/CCP4), R8.2 (E)
unnamed: PIC1.17 (RC6/CANTX/TX1/CK1/CCP3), R7.2 (E)
unnamed: C33.1, PIC1.10 (OSC2/CLKOUT/RA6), Q1.2
unnamed: PIC1.16 (RC5/SDO), R6.2 (E)
unnamed: PIC1.15 (RC4/SDI/SDA), R5.2 (E)
unnamed: PIC1.14 (RC3/REFO/SCK/SCL), R4.2 (E)
unnamed: PIC1.13 (RC2/CCP2/T1G), R3.2 (E)
unnamed: PIC1.12 (RC1/ISOSCI), R2.2 (E)
unnamed: PIC1.11 (RC0/SOSCO/SCLKI), R1.2 (E)
unnamed: CANIC_1.4 (04_RXD), CRX.K (C), PIC1.24 (RB3/CANRX/INT3/C2OUT/P1D/CTED2)
unnamed: PIC1.4 (RA2/AN2/VREF-), R15.2 (E)
unnamed: C5.1, PIC1.5 (RA3/AN3/VREF+), PIC1.7 (RA5/AN4/~SS/HLVDIN/CTMUI/T1CKI/C2INB)
unnamed: PIC1.21 (RB0/INT0/FLT0/C1INA/AN10), R9.2 (E)
unnamed: PIC1.22 (RB1/INT1/AN8/C1INB/P1B/CTDIN), R10.2 (E)
unnamed: U$1.P$5, X2.1
unnamed: U$1.P$4, X2.2
unnamed: U$1.P$3, X2.3
unnamed: PIC1.2 (RA0/CVREF/AN0/ULPWU), R13.2 (E)
unnamed: U$1.P$2, X2.6
unnamed: PIC1.3 (RA1/AN1), R14.2 (E)
unnamed: PIC1.25 (RB4/AN9/C2INA/ECCP1/P1A/CTPLS/KBI0), R11.2 (E)
unnamed: C34.1, PIC1.9 (OSC1/CLKIN/RA7), Q1.1
unnamed: CN3.5, IC1.2 (!RE), IC1.3 (DE), PIC1.27 (RB6/PGC/TX2/CK2/KBI2), SJ2.3 (1), SJ3.3 (1)
unnamed: C38.2, PIC1.6 (VDDCORE/VCAP)
unnamed: CN3.4, IC1.1 (R), IC1.4 (D), PIC1.28 (RB7/PGD/T3G/RX2/DT2/KBI3), SJ3.2
VDD: C4.P+, D1.P$2 (C), U$2.P$2, U$6.P$2 (2_+VIN)
VSS: C4.P-, U$2.P$1, U$6.P$1 (1_-VIN), X2.7

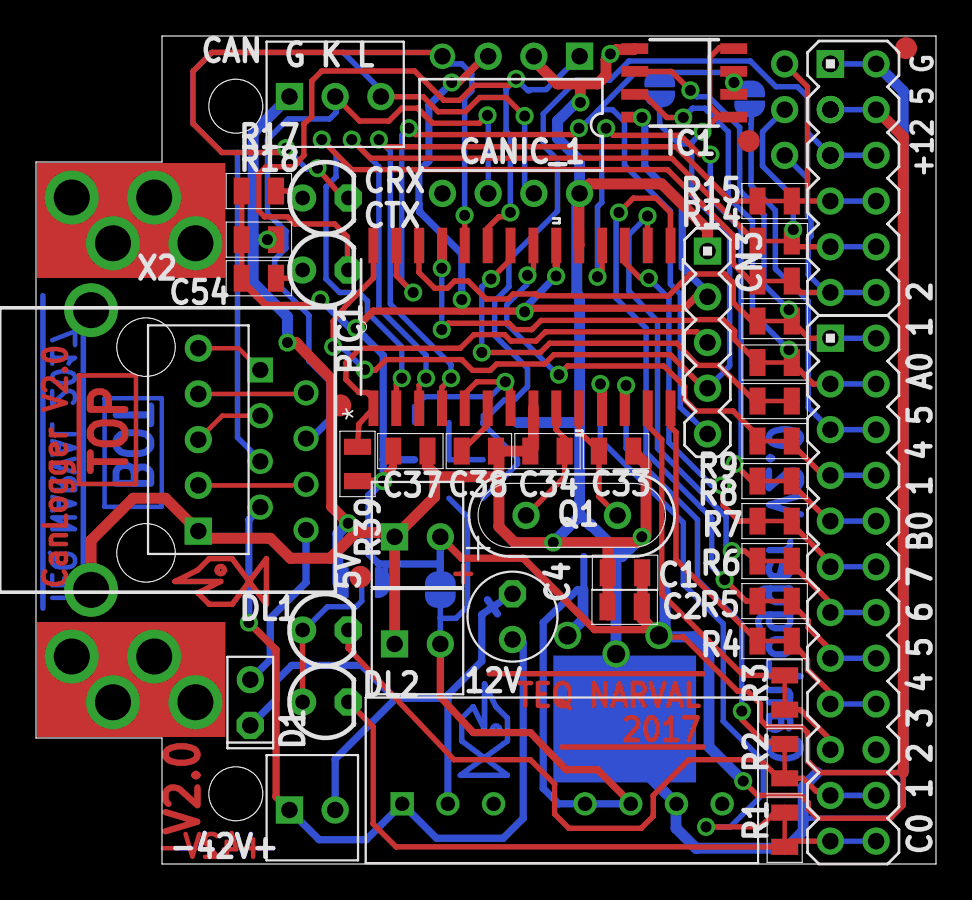
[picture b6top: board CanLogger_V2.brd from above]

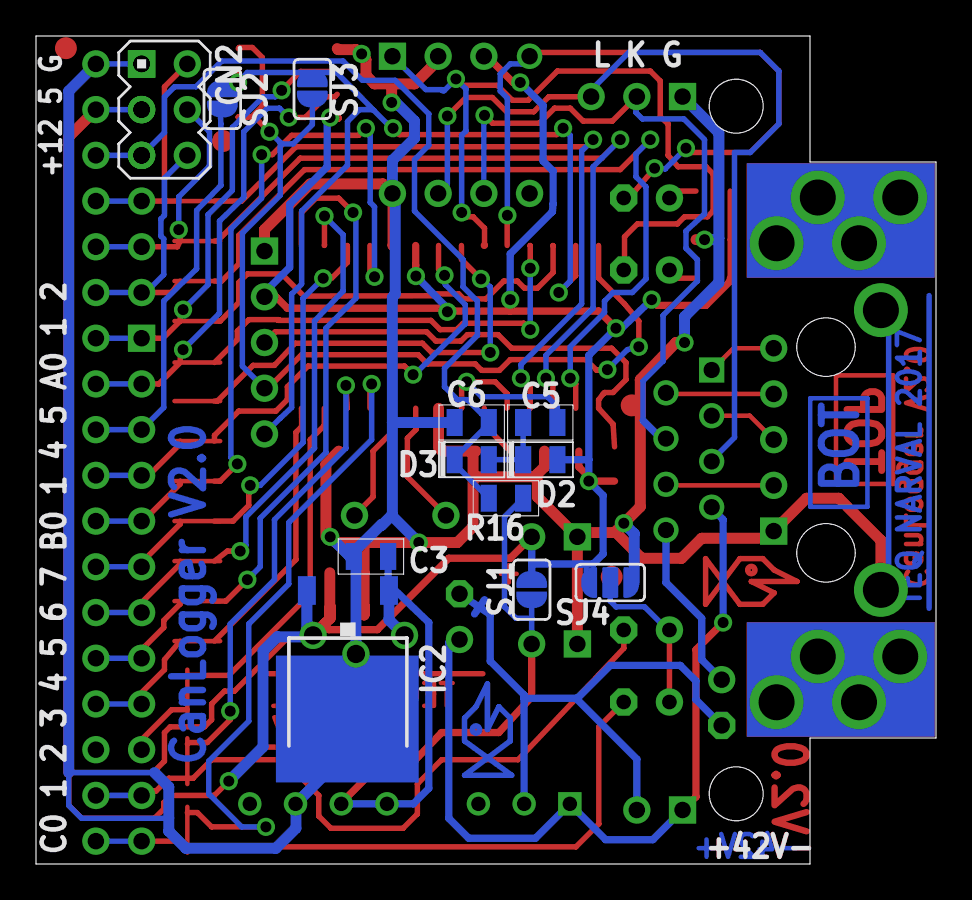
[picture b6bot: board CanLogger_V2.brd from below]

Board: 2 copper layers, 50.0 x 46.0 mm, 57 parts (12 on the bottom side), 56 nets.

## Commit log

2022-09-01 fajlok hozzaadva
2022-09-01 ujabb fajlok hozzadva
2022-09-01 ujabb fajlok hozzaadva
2022-09-01 hh-08 hozzaadva
2022-09-02 stopper qfn-re áttervezve
2022-09-02 fenyjelzo elkezdve
2022-09-04 fenyjelzo 90%os lett
2022-09-04 mtx12 30% kesz
2022-09-06 munka_szept_6
2022-09-06 streamnet hozzaadva
2022-09-06 stream_haladás
2022-09-06 eredetiek feltöltve
2022-09-07 streamnet ssopsodott
2022-09-07 stream testatkot megszunt
2022-09-07 javult meg ez az
2022-09-08 diodak felkerultek
2022-09-08 stream finish
2022-09-09 Streamnet finished
2022-09-09 stopper elkeszult
